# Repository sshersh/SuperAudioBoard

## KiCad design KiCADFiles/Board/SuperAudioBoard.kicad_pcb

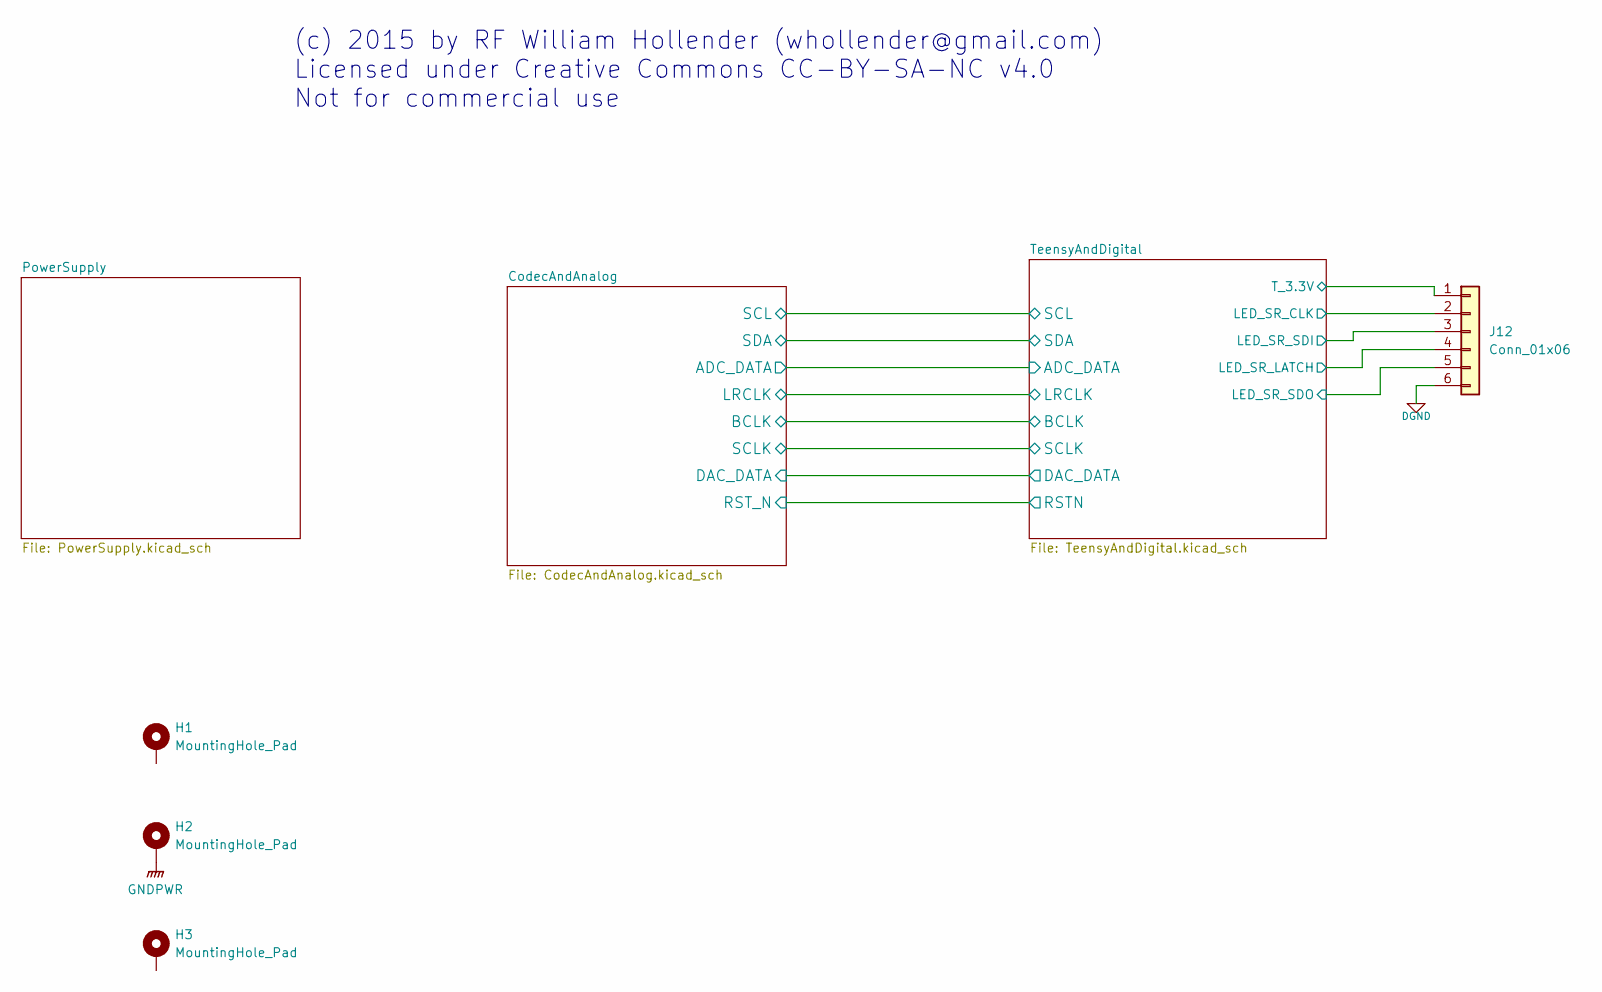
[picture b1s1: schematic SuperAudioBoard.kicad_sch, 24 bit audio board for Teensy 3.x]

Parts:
H1, H2, H3: MountingHole_Pad; MountingHole_3.2mm_M3_DIN965_Pad
J12: Conn_01x06; JST_EH_B6B-EH-A_1x06_P2.50mm_Vertical

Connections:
/TeensyAndDigital/LED_SR_CLK: J12.2; also elsewhere on the board
/TeensyAndDigital/LED_SR_LATCH: J12.4; also elsewhere on the board
/TeensyAndDigital/LED_SR_SDI: J12.3; also elsewhere on the board
/TeensyAndDigital/LED_SR_SDO: J12.5; also elsewhere on the board
/TeensyAndDigital/T_3.3V: J12.1; also elsewhere on the board
DGND: J12.6; also elsewhere on the board
GNDPWR: H2.1; also elsewhere on the board

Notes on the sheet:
(c) 2015 by RF William Hollender (whollender@gmail.com) Licensed under Creative Commons CC-BY-SA-NC v4.0 Not for commercial use

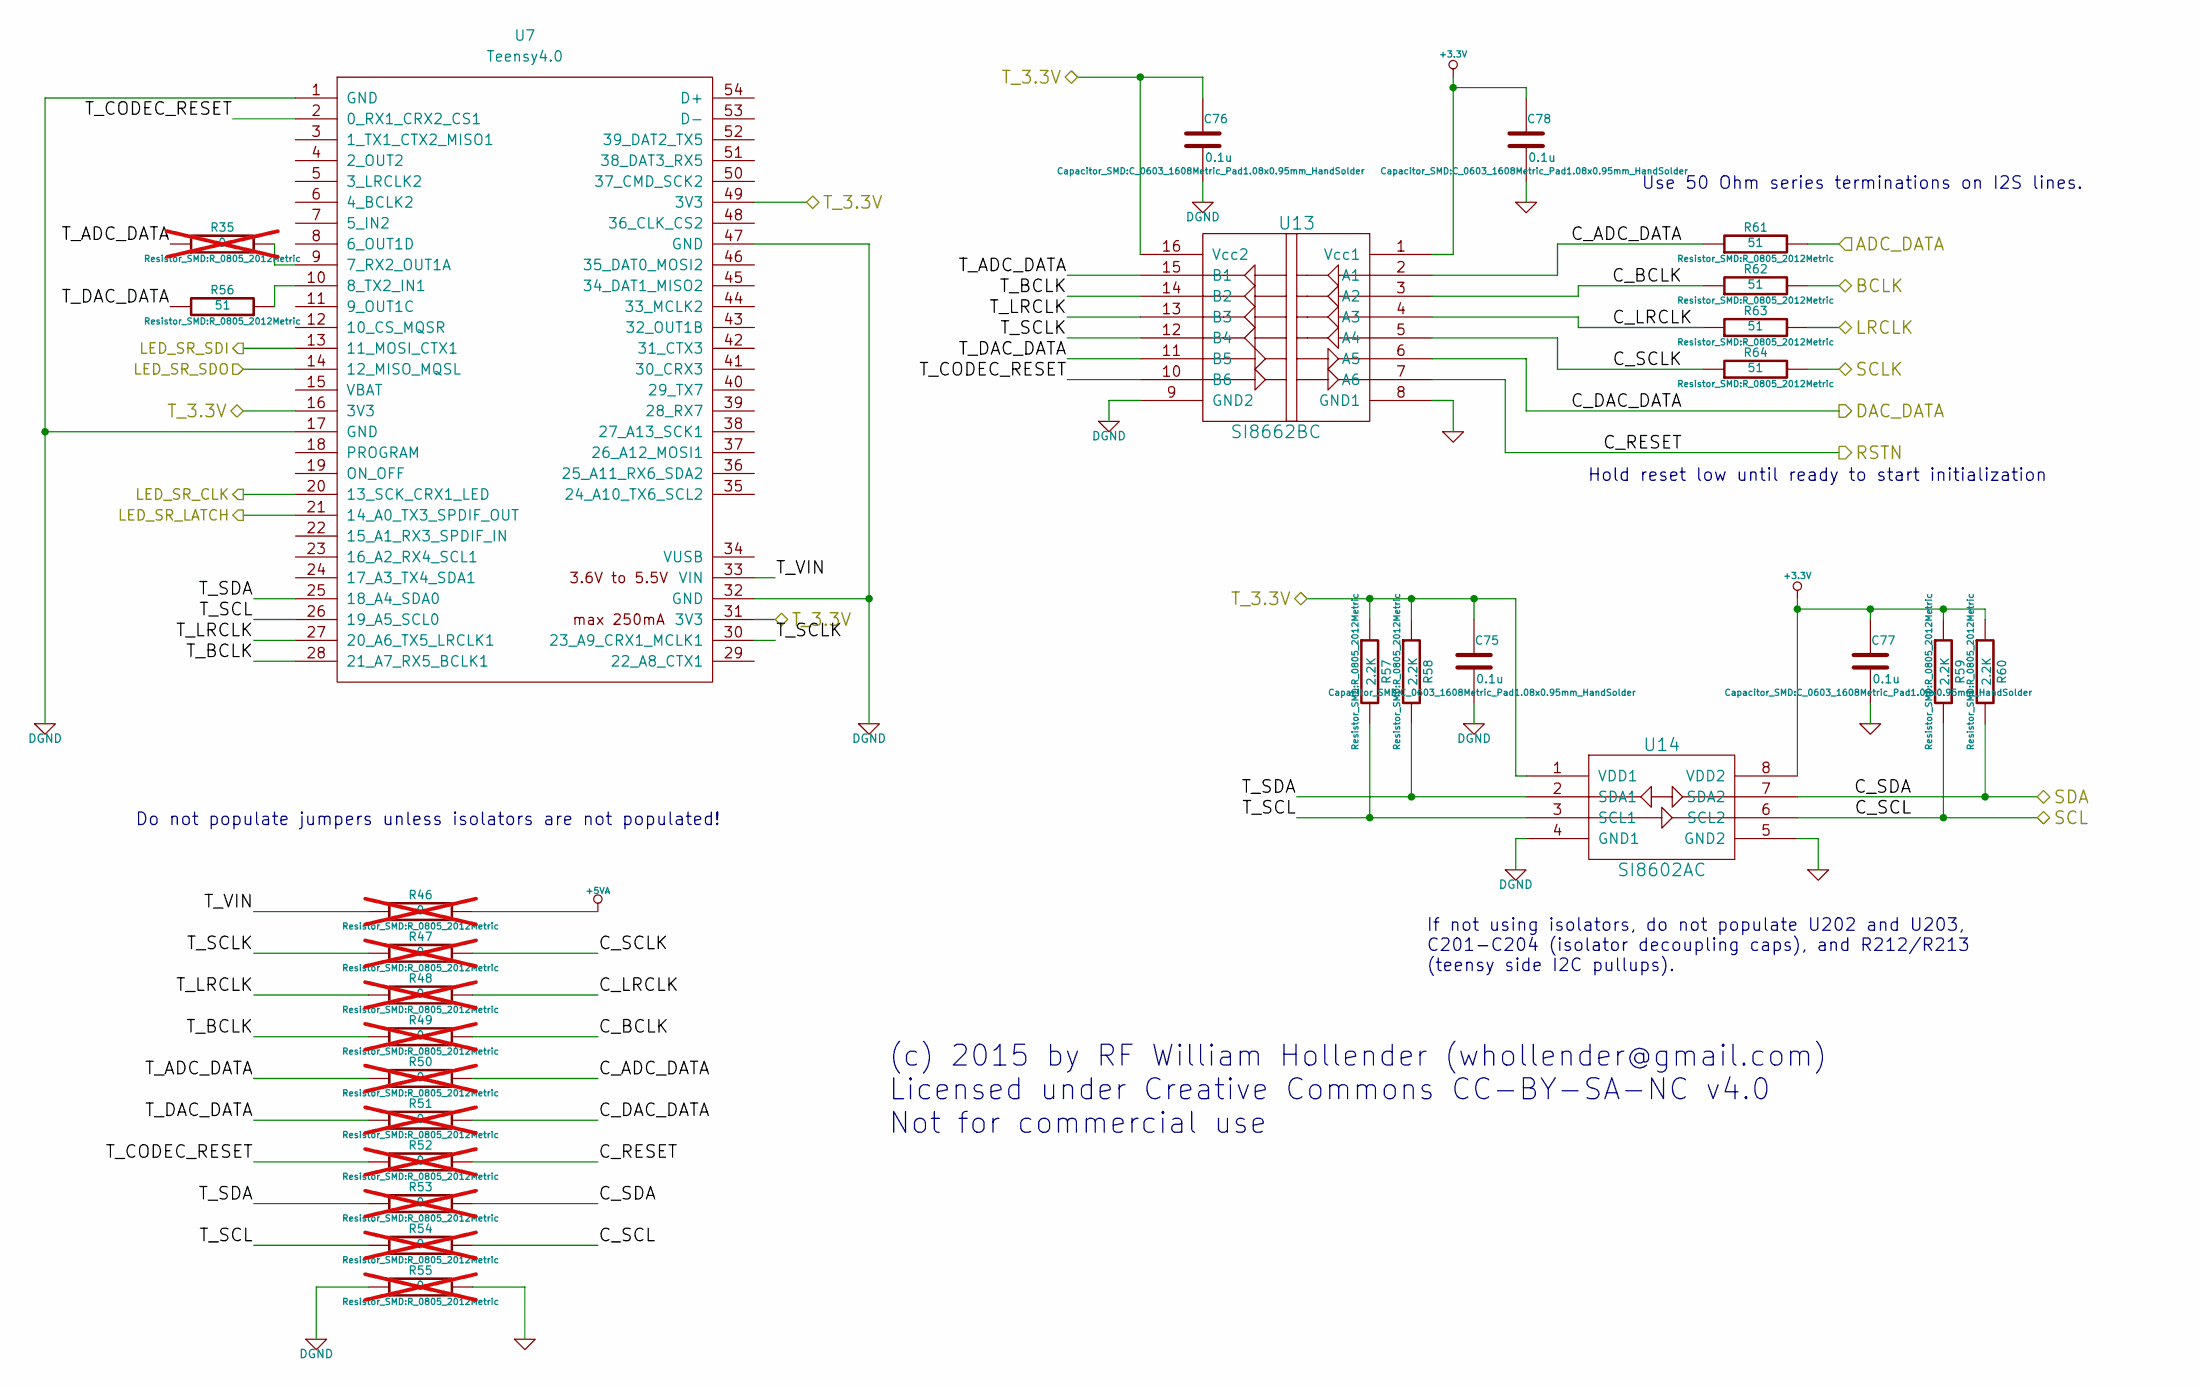
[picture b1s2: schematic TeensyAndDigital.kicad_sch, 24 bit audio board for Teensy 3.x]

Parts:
C75, C76, C77, C78: 0.1u; C_0603_1608Metric_Pad1.08x0.95mm_HandSolder; MFG1 PN GRM188R71E104KA01
R35, R46, R47, R48, R49, R50, R51, R52, R53, R54, R55: 0; R_0805_2012Metric; MFG1 PN RC0805JR-070RL; not fitted
R56, R61, R62, R63, R64: 51; R_0805_2012Metric; MFG1 PN CRCW080551R0JNEA
R57, R58, R59, R60: 2.2K; R_0805_2012Metric; MFG1 PN RC0805JR-072K2L
U7: Teensy4.0; Teensy40; MPN Teensy4.0
U13: SI8662BC; SOIC-16W_7.5x10.3mm_P1.27mm; MFG1 PN SI8662BC
U14: SI8602AC; SOIC-8_3.9x4.9mm_P1.27mm; MFG1 PN SI8602AC

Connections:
+3.3V: C77.1, C78.1, R59.1, R60.1, U13.1 (Vcc1), U14.8 (VDD2); also elsewhere on the board
+5VA: R46.2; also elsewhere on the board
/CodecAndAnalog/ADC_DATA: R61.2; also elsewhere on the board
/CodecAndAnalog/BCLK: R62.2; also elsewhere on the board
/CodecAndAnalog/LRCLK: R63.2; also elsewhere on the board
/CodecAndAnalog/SCLK: R64.2; also elsewhere on the board
/TeensyAndDigital/C_ADC_DATA: R50.2, R61.1, U13.2 (A1)
/TeensyAndDigital/C_BCLK: R49.2, R62.1, U13.3 (A2)
/TeensyAndDigital/C_DAC_DATA: R51.2, U13.6 (A5); also elsewhere on the board
/TeensyAndDigital/C_LRCLK: R48.2, R63.1, U13.4 (A3)
/TeensyAndDigital/C_RESET: R52.2, U13.7 (A6); also elsewhere on the board
/TeensyAndDigital/C_SCL: R54.2, R59.2, U14.6 (SCL2); also elsewhere on the board
/TeensyAndDigital/C_SCLK: R47.2, R64.1, U13.5 (A4)
/TeensyAndDigital/C_SDA: R53.2, R60.2, U14.7 (SDA2); also elsewhere on the board
/TeensyAndDigital/LED_SR_CLK: U7.20 (13_SCK_CRX1_LED); also elsewhere on the board
/TeensyAndDigital/LED_SR_LATCH: U7.21 (14_A0_TX3_SPDIF_OUT); also elsewhere on the board
/TeensyAndDigital/LED_SR_SDI: U7.13 (11_MOSI_CTX1); also elsewhere on the board
/TeensyAndDigital/LED_SR_SDO: U7.14 (12_MISO_MQSL); also elsewhere on the board
/TeensyAndDigital/T_3.3V: C75.1, C76.1, R57.1, R58.1, U7.16 (3V3), U7.31 (3V3), U7.49 (3V3), U13.16 (Vcc2), U14.1 (VDD1); also elsewhere on the board
/TeensyAndDigital/T_ADC_DATA: R35.1, R50.1, U13.15 (B1)
/TeensyAndDigital/T_BCLK: R49.1, U7.28 (21_A7_RX5_BCLK1), U13.14 (B2)
/TeensyAndDigital/T_CODEC_RESET: R52.1, U7.2 (0_RX1_CRX2_CS1), U13.10 (B6)
/TeensyAndDigital/T_DAC_DATA: R51.1, R56.2, U13.11 (B5)
/TeensyAndDigital/T_LRCLK: R48.1, U7.27 (20_A6_TX5_LRCLK1), U13.13 (B3)
/TeensyAndDigital/T_SCL: R54.1, R57.2, U7.26 (19_A5_SCL0), U14.3 (SCL1)
/TeensyAndDigital/T_SCLK: R47.1, U7.30 (23_A9_CRX1_MCLK1), U13.12 (B4)
/TeensyAndDigital/T_SDA: R53.1, R58.2, U7.25 (18_A4_SDA0), U14.2 (SDA1)
/TeensyAndDigital/T_VIN: R46.1, U7.33 (VIN)
DGND: C75.2, C76.2, R55.1, U7.1 (GND), U7.17 (GND), U7.32 (GND), U7.47 (GND), U13.9 (GND2), U14.4 (GND1); also elsewhere on the board
GND: C77.2, C78.2, R55.2, U13.8 (GND1), U14.5 (GND2); also elsewhere on the board
unnamed: R35.2, U7.9 (7_RX2_OUT1A)
unnamed: R56.1, U7.10 (8_TX2_IN1)

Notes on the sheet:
Do not populate jumpers unless isolators are not populated!
(c) 2015 by RF William Hollender (whollender@gmail.com) Licensed under Creative Commons CC-BY-SA-NC v4.0 Not for commercial use
If not using isolators, do not populate U202 and U203, C201-C204 (isolator decoupling caps), and R212/R213 (teensy side I2C pullups).
Use 50 Ohm series terminations on I2S lines.
Hold reset low until ready to start initialization

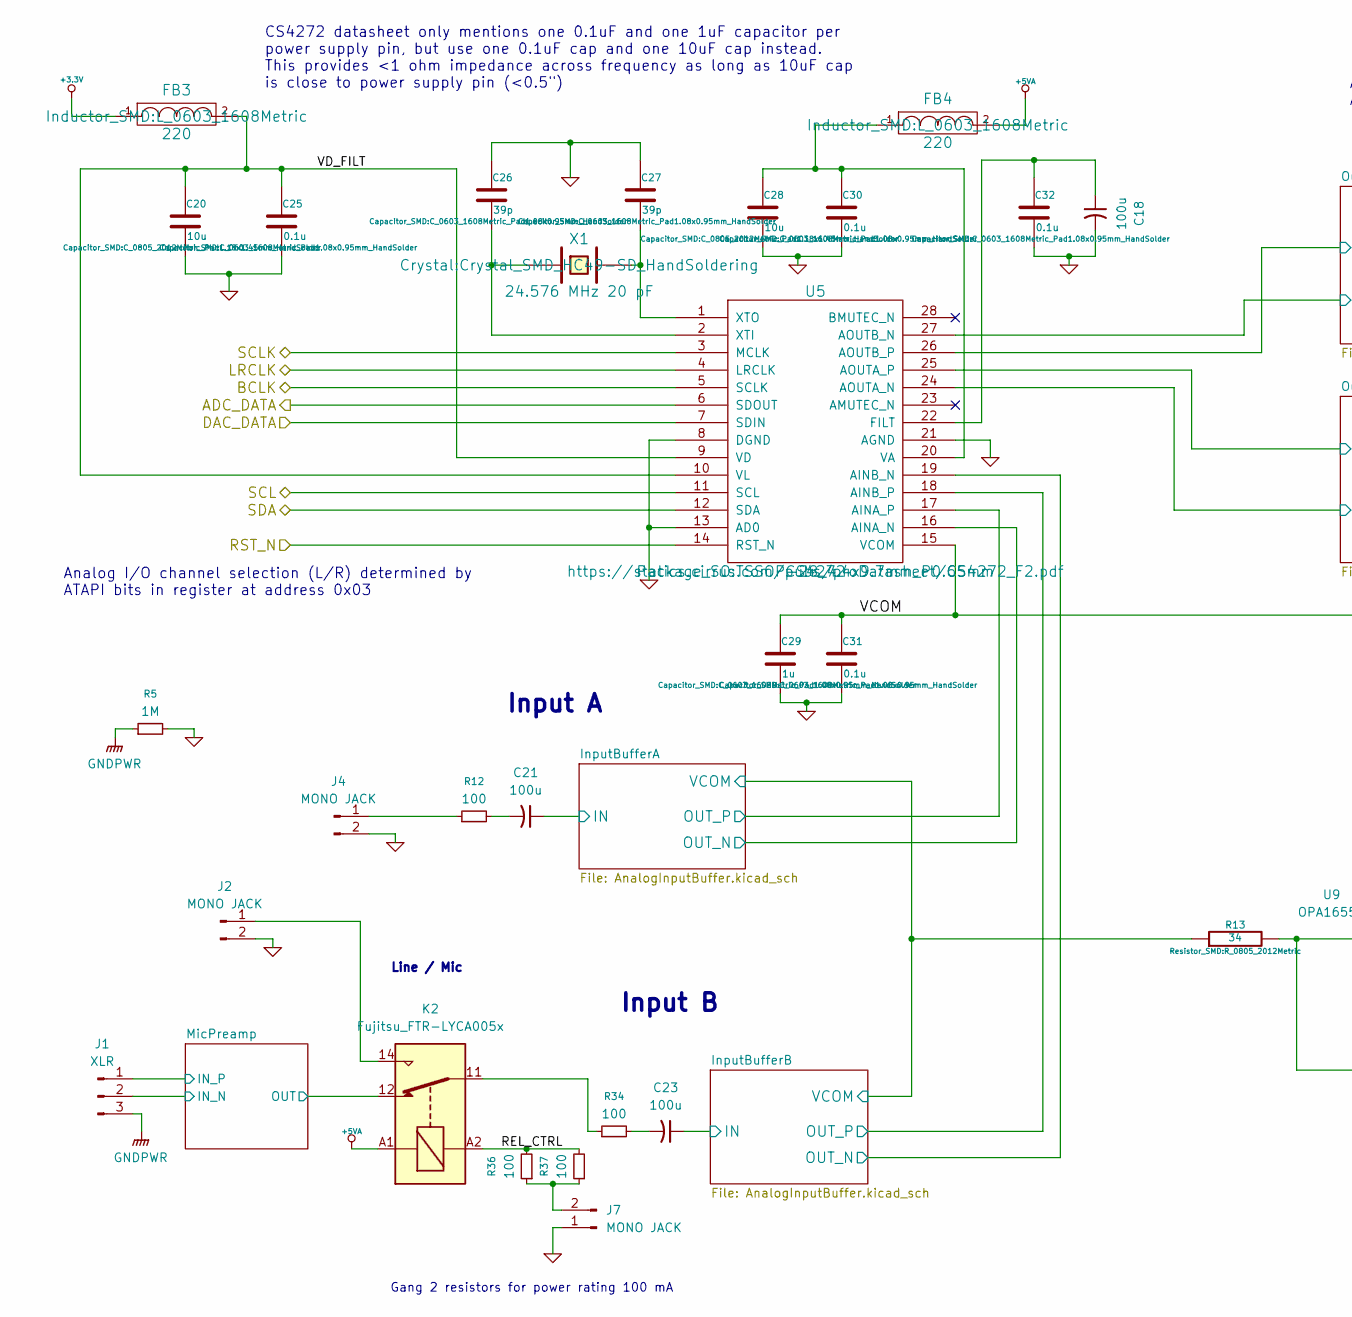
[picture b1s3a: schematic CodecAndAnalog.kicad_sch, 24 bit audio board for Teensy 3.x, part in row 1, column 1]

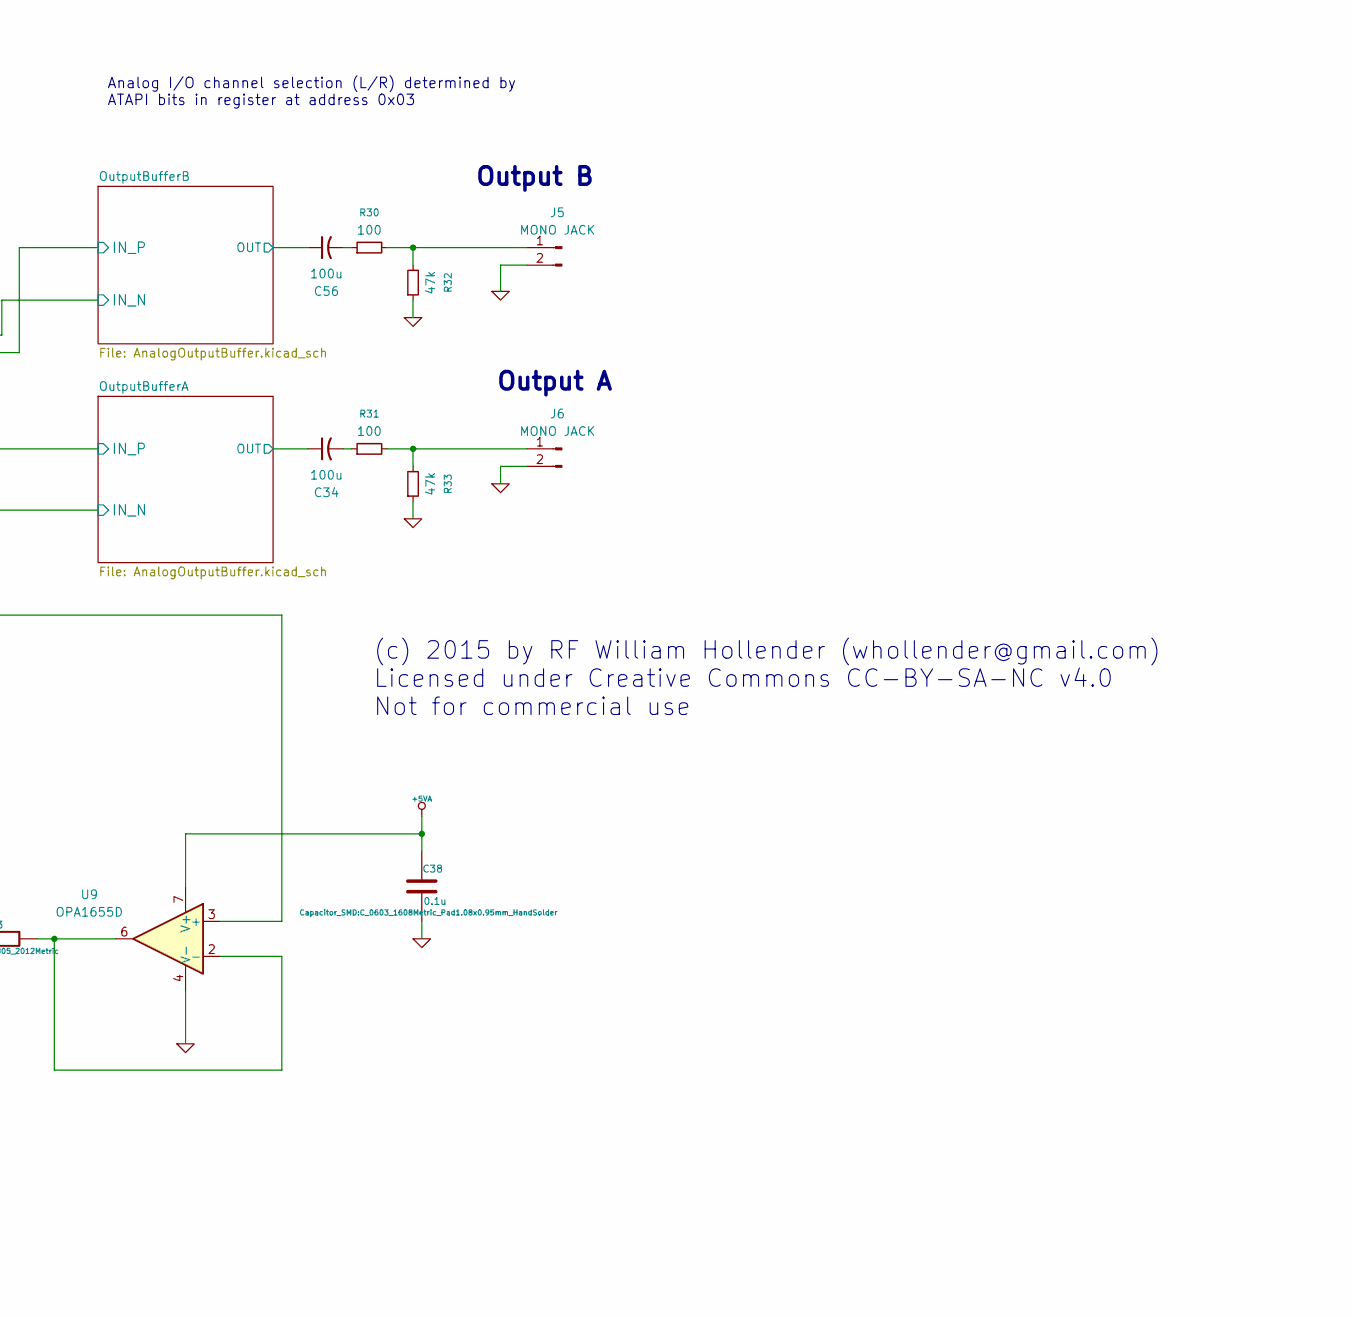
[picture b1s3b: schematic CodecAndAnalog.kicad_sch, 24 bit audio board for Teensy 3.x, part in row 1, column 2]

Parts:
C18, C21, C23, C34, C56: 100u; CP_Radial_D5.0mm_P2.00mm; MPN 25PX100MEFC5X11
C20, C28: 10u; C_0805_2012Metric_Pad1.18x1.45mm_HandSolder; Voltage 25V; MFG1 PN GRM32DR71E106KA12
C25, C30, C31, C32, C38: 0.1u; C_0603_1608Metric_Pad1.08x0.95mm_HandSolder; MFG1 PN GRM188R71E104KA01
C26, C27: 39p; C_0603_1608Metric_Pad1.08x0.95mm_HandSolder; MFG1 PN GRM1885C1H390JA01D
C29: 1u; C_0603_1608Metric_Pad1.08x0.95mm_HandSolder; MFG1 PN C2012X7R1E105K125AB
FB3, FB4: 220; L_0603_1608Metric; MFG1 PN BLM18AG221SN1
J1: XLR; PinHeader_1x03_P2.54mm_Vertical
J2, J4, J5, J6, J7: MONO JACK; PinHeader_1x02_P2.54mm_Vertical
K2: Fujitsu_FTR-LYCA005x; Relay_SPDT_Fujitsu_FTR-LYCA005x_FormC_Vertical
R5: 1M; R_0805_2012Metric
R12, R30, R31, R34, R36, R37: 100; R_0805_2012Metric; MPN CRCW0805100RFKEA
R13: 34; R_0805_2012Metric; MFG1 PN RC0805JR-0710RL
R32, R33: 47k; R_0805_2012Metric; MPN RC0805FR-0747KL
U5: CS4272; TSSOP-28_4.4x9.7mm_P0.65mm; MFG1 PN CS4272-CZZ
U9: OPA1655D; SOIC-8_3.9x4.9mm_P1.27mm; MPN OPA1655D
X1: 24.576 MHz 20 pF; Crystal_SMD_HC49-SD_HandSoldering; MFG1 PN ABM3-24.576MHZ-B2-T

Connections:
+3.3V: FB3.1; also elsewhere on the board
+5VA: C38.1, FB4.2, K2.A1, U9.7 (V+); also elsewhere on the board
/CodecAndAnalog/ADC_DATA: U5.6 (SDOUT); also elsewhere on the board
/CodecAndAnalog/BCLK: U5.5 (SCLK); also elsewhere on the board
/CodecAndAnalog/InputBufferA/OUT_N: U5.16 (AINA_N); also elsewhere on the board
/CodecAndAnalog/InputBufferA/OUT_P: U5.17 (AINA_P); also elsewhere on the board
/CodecAndAnalog/InputBufferA/VCOM: R13.1; also elsewhere on the board
/CodecAndAnalog/InputBufferA/VSIGIN: C21.1; also elsewhere on the board
/CodecAndAnalog/InputBufferB/OUT_N: U5.19 (AINB_N); also elsewhere on the board
/CodecAndAnalog/InputBufferB/OUT_P: U5.18 (AINB_P); also elsewhere on the board
/CodecAndAnalog/InputBufferB/VSIGIN: C23.1; also elsewhere on the board
/CodecAndAnalog/LRCLK: U5.4 (LRCLK); also elsewhere on the board
/CodecAndAnalog/MicPreamp/IN_N: J1.2; also elsewhere on the board
/CodecAndAnalog/MicPreamp/IN_P: J1.1; also elsewhere on the board
/CodecAndAnalog/MicPreamp/OUT: K2.12; also elsewhere on the board
/CodecAndAnalog/OutputBufferA/IN_N: U5.24 (AOUTA_N); also elsewhere on the board
/CodecAndAnalog/OutputBufferA/IN_P: U5.25 (AOUTA_P); also elsewhere on the board
/CodecAndAnalog/OutputBufferA/OUT: C34.1; also elsewhere on the board
/CodecAndAnalog/OutputBufferB/IN_N: U5.27 (AOUTB_N); also elsewhere on the board
/CodecAndAnalog/OutputBufferB/IN_P: U5.26 (AOUTB_P); also elsewhere on the board
/CodecAndAnalog/OutputBufferB/OUT: C56.1; also elsewhere on the board
/CodecAndAnalog/REL_CTRL: K2.A2, R36.2, R37.2
/CodecAndAnalog/SCLK: U5.3 (MCLK); also elsewhere on the board
/CodecAndAnalog/VCOM: C29.1, C31.1, U5.15 (VCOM), U9.3 (+)
/CodecAndAnalog/VD_FILT: C20.1, C25.1, FB3.2, U5.9 (VD), U5.10 (VL)
/TeensyAndDigital/C_DAC_DATA: U5.7 (SDIN); also elsewhere on the board
/TeensyAndDigital/C_RESET: U5.14 (RST_N); also elsewhere on the board
/TeensyAndDigital/C_SCL: U5.11 (SCL); also elsewhere on the board
/TeensyAndDigital/C_SDA: U5.12 (SDA); also elsewhere on the board
GND: C18.2, C20.2, C25.2, C26.1, C27.1, C28.2, C29.2, C30.2, C31.2, C32.2, C38.2, J2.2, J4.2, J5.2, J6.2, J7.1, R5.2, R32.1, R33.1, U5.8 (DGND), U5.13 (AD0), U5.21 (AGND), U9.4 (V-); also elsewhere on the board
GNDPWR: J1.3, R5.1; also elsewhere on the board
unnamed: C21.2, R12.2
unnamed: C23.2, R34.2
unnamed: C34.2, R31.1
unnamed: C56.2, R30.1
unnamed: J2.1, K2.14
unnamed: J4.1, R12.1
unnamed: J5.1, R30.2, R32.2
unnamed: J6.1, R31.2, R33.2
unnamed: J7.2, R36.1, R37.1
unnamed: K2.11, R34.1
unnamed: C18.1, C32.1, U5.22 (FILT)
unnamed: C28.1, C30.1, FB4.1, U5.20 (VA)
unnamed: C26.2, U5.2 (XTI), X1.1
unnamed: C27.2, U5.1 (XTO), X1.2
unnamed: R13.2, U9.2 (-), U9.6

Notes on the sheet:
Gang 2 resistors for power rating 100 mA
Output B
CS4272 datasheet only mentions one 0.1uF and one 1uF capacitor per power supply pin, but use one 0.1uF cap and one 10uF cap instead. This provides <1 ohm impedance across frequency as long as 10uF cap is close to power supply pin (<0.5")
Input B
(c) 2015 by RF William Hollender (whollender@gmail.com) Licensed under Creative Commons CC-BY-SA-NC v4.0 Not for commercial use
Analog I/O channel selection (L/R) determined by ATAPI bits in register at address 0x03
Line / Mic
Output A
Input A

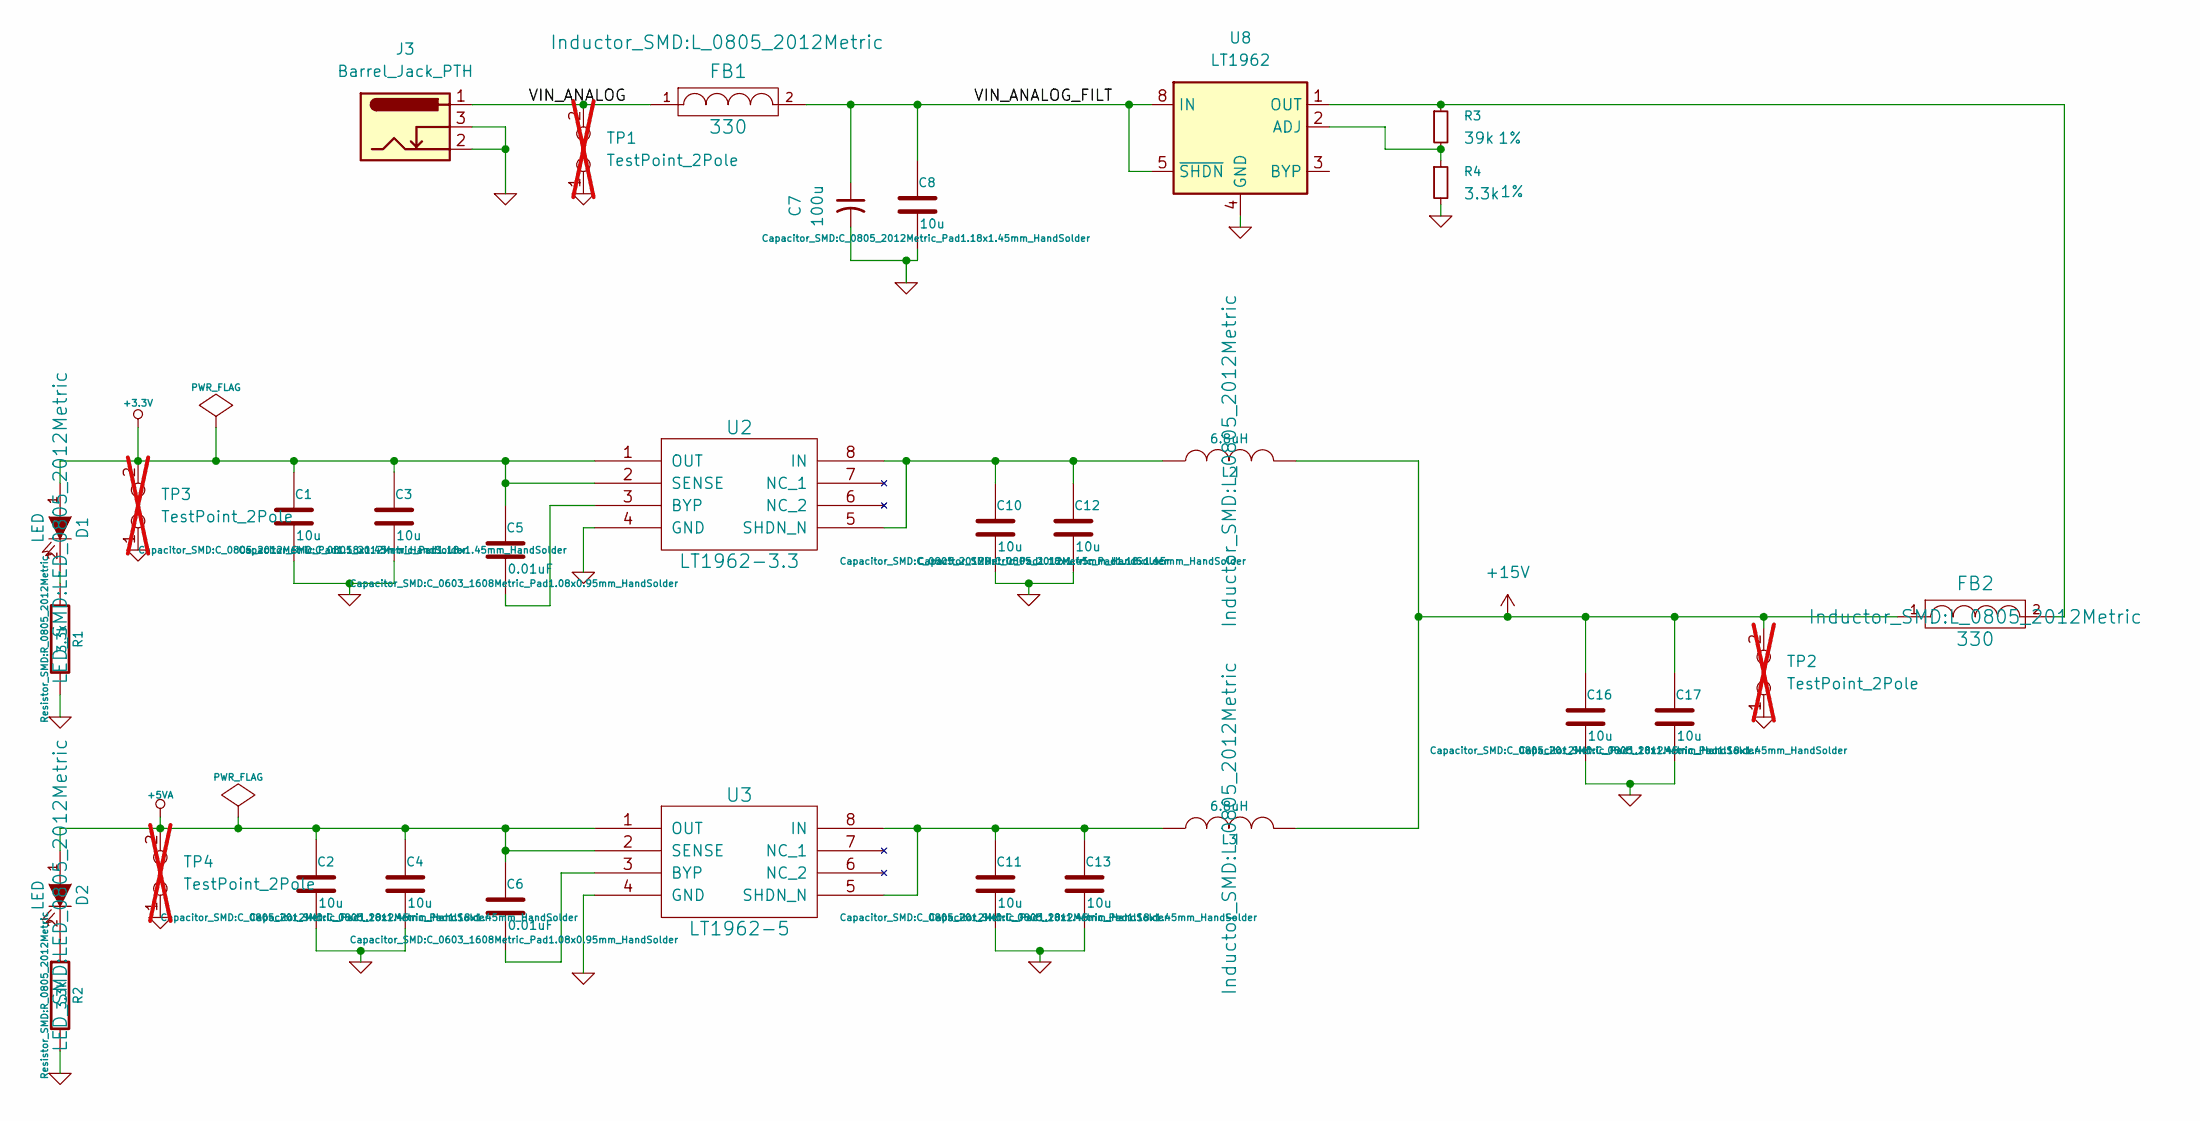
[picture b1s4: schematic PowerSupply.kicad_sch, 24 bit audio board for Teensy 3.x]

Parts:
C1, C2, C3, C4, C8, C10, C11, C12, C13, C16, C17: 10u; C_0805_2012Metric_Pad1.18x1.45mm_HandSolder; Voltage 25V; MFG1 PN GRM32DR71E106KA12
C5, C6: 0.01uF; C_0603_1608Metric_Pad1.08x0.95mm_HandSolder; MFG1 PN GRM2195C1H103JA01D
C7: 100u; CP_Radial_D5.0mm_P2.00mm; MPN 25PX100MEFC5X11
D1, D2: LED; LED_0805_2012Metric; MFG1 PN APT2012CGCK
FB1, FB2: 330; L_0805_2012Metric; MFG1 PN BLM21PG331SN1D
J3: Barrel_Jack_PTH
L2, L3: 6.8uH; L_0805_2012Metric; MFG1 PN MSS1038-522NLB
R1: 3.3k; R_0805_2012Metric; MFG1 PN ERJ-6GEYJ271V
R2: 3.3k; R_0805_2012Metric; MFG1 PN ERJ-6GEYJ621V
R3: 39k; R_0805_2012Metric; MPN ERA-6AEB3922V
R4: 3.3k; R_0805_2012Metric; MPN ERA-6AEB332V
TP1, TP2, TP3, TP4: TestPoint_2Pole; TestPoint_2Pads_Pitch2.54mm_Drill0.8mm; not fitted
U2: LT1962-3.3; MSOP-8_3x3mm_P0.65mm; MFG1 PN LT1962EMS8-3.3#PBF
U3: LT1962-5; MSOP-8_3x3mm_P0.65mm; MFG1 PN LT1962EMS8-5#PBF-ND
U8: LT1962; MSOP-8_3x3mm_P0.65mm; MPN LT1962EMS8

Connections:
+3.3V: C1.1, C3.1, C5.1, D1.1 (A), TP3.2, U2.1 (OUT), U2.2 (SENSE); also elsewhere on the board
+5VA: C2.1, C4.1, C6.1, D2.1 (A), TP4.2, U3.1 (OUT), U3.2 (SENSE); also elsewhere on the board
+15V: C16.1, C17.1, FB2.1, L2.2, L3.2, TP2.2; also elsewhere on the board
/PowerSupply/VIN_ANALOG: FB1.1, J3.1 (PWR), TP1.2
/PowerSupply/VIN_ANALOG_FILT: C7.1, C8.1, FB1.2, U8.5 (~SHDN), U8.8 (IN)
GND: C1.2, C2.2, C3.2, C4.2, C7.2, C8.2, C10.2, C11.2, C12.2, C13.2, C16.2, C17.2, J3.2 (GND), J3.3 (GNDBREAK), R1.2, R2.2, R4.2, TP1.1, TP2.1, TP3.1, TP4.1, U2.4 (GND), U3.4 (GND), U8.4 (GND); also elsewhere on the board
unnamed: D1.2 (K), R1.1
unnamed: D2.2 (K), R2.1
unnamed: C5.2, U2.3 (BYP)
unnamed: C10.1, C12.1, L2.1, U2.5 (SHDN_N), U2.8 (IN)
unnamed: C6.2, U3.3 (BYP)
unnamed: C11.1, C13.1, L3.1, U3.5 (SHDN_N), U3.8 (IN)
unnamed: R3.2, R4.1, U8.2 (ADJ)
unnamed: FB2.2, R3.1, U8.1 (OUT)

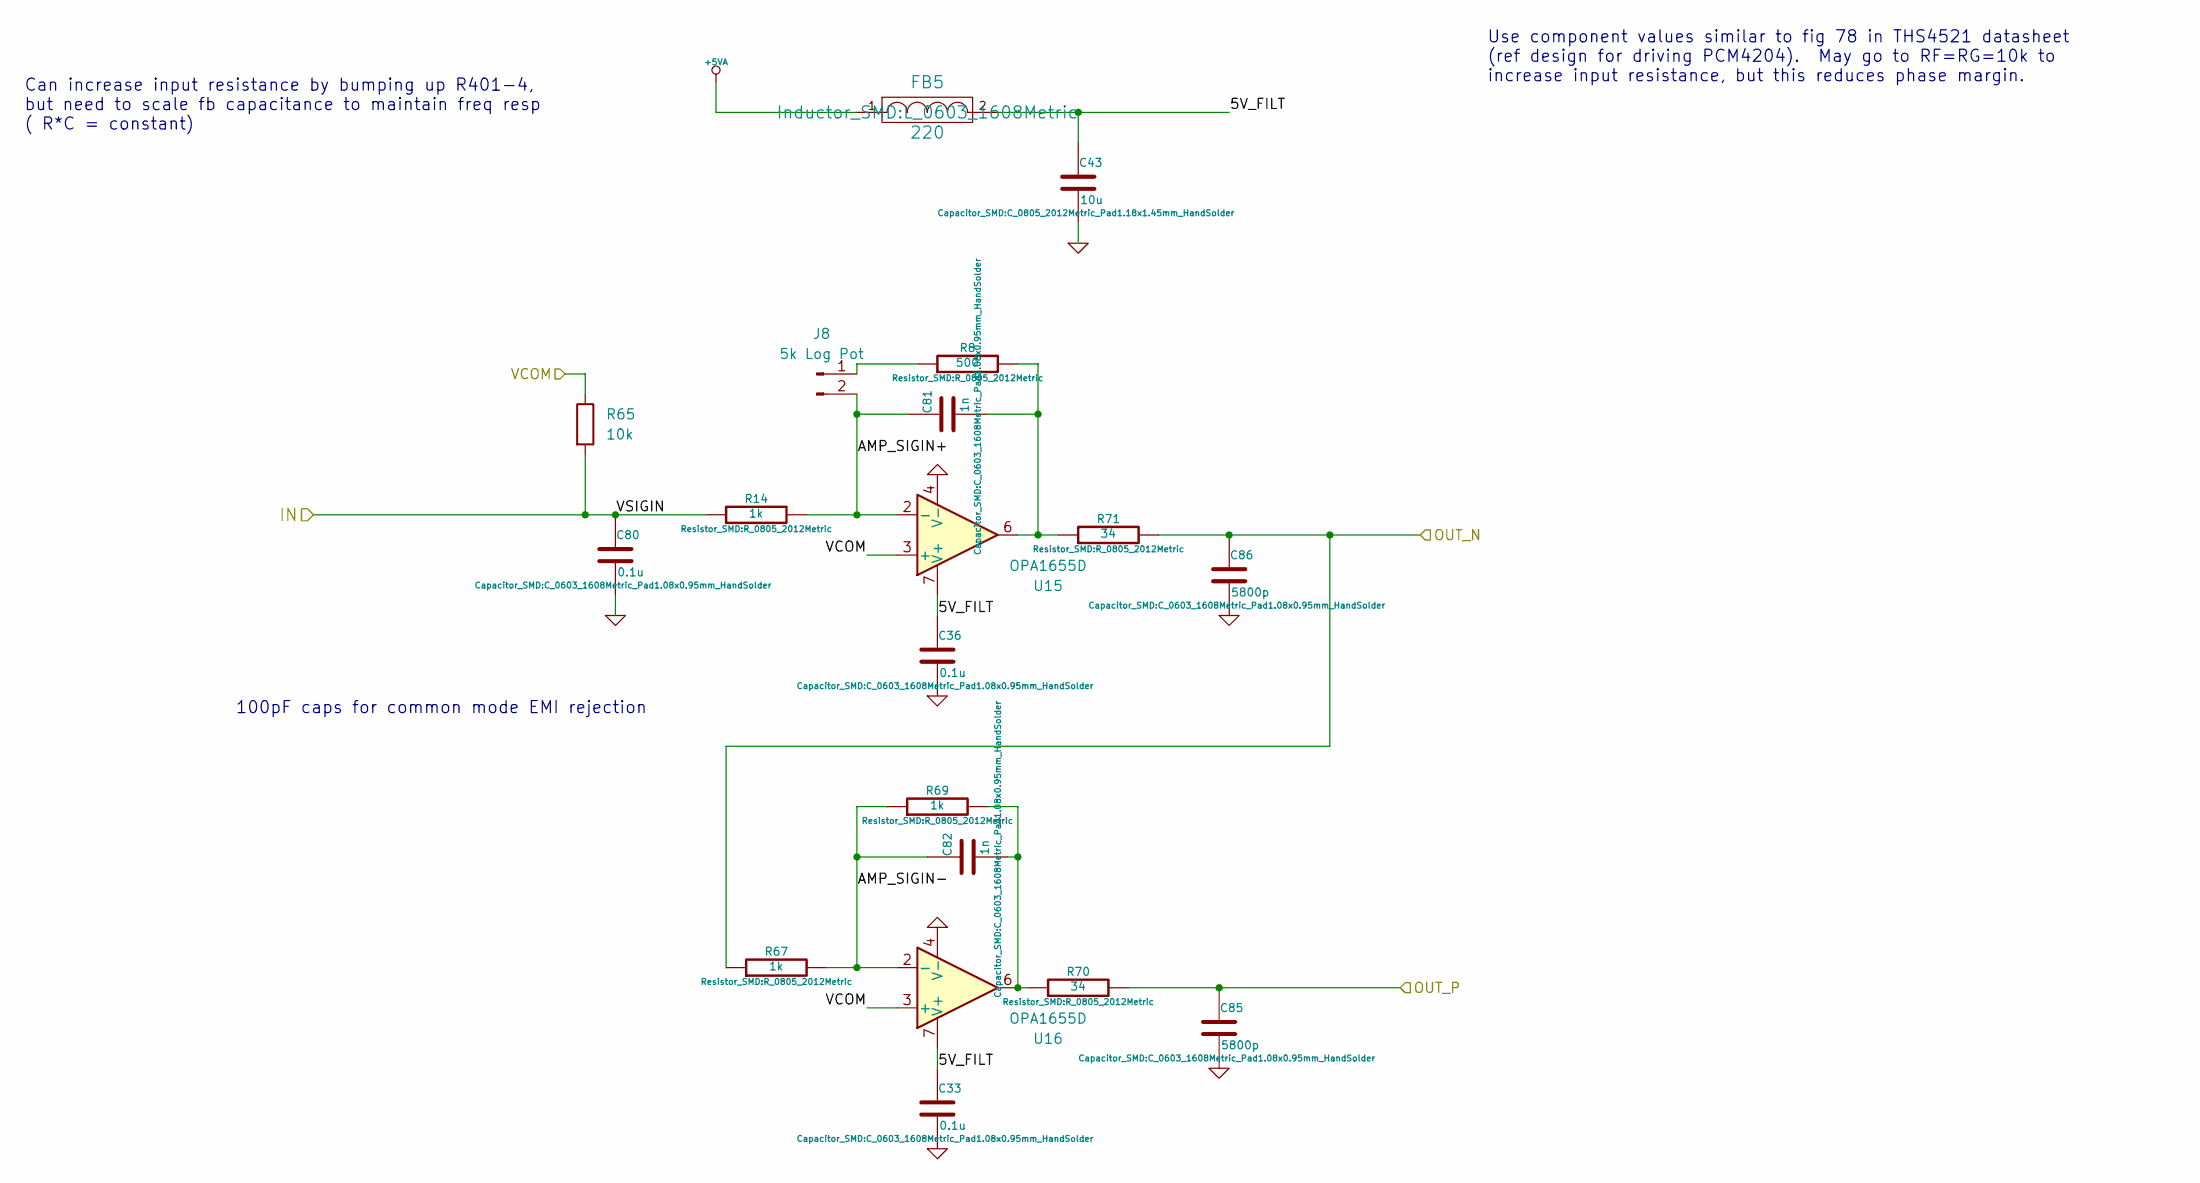
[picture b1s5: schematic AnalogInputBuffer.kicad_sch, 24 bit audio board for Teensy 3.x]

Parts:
C33, C36: 0.1u; C_0603_1608Metric_Pad1.08x0.95mm_HandSolder; MFG1 PN GRM188R71E104KA01
C43: 10u; C_0805_2012Metric_Pad1.18x1.45mm_HandSolder; Voltage 25V; MFG1 PN GRM32DR71E106KA12
C80: 0.1u; C_0603_1608Metric_Pad1.08x0.95mm_HandSolder; MFG1 PN GRM1885C1H101JA01D
C81, C82: 1n; C_0603_1608Metric_Pad1.08x0.95mm_HandSolder; MFG1 PN GRM2165C1H102FA01D
C85, C86: 5800p; C_0603_1608Metric_Pad1.08x0.95mm_HandSolder; MFG1 PN GRM2165C1H272JA01D
FB5: 220; L_0603_1608Metric; MFG1 PN BLM18AG221SN1
J8: 5k Log Pot; PinHeader_1x02_P2.54mm_Vertical; MPN RV16AF-10-15K-C5K-3LA
R8: 500; R_0805_2012Metric; MFG1 PN RG2012P-102-B-T5
R14, R67, R69: 1k; R_0805_2012Metric; MFG1 PN RG2012P-102-B-T5
R65: 10k; R_0805_2012Metric; MPN CRCW080510K0FKEA
R70, R71: 34; R_0805_2012Metric; MFG1 PN RR1220Q-40R2-D-M
U15, U16: OPA1655D; SOIC-8_3.9x4.9mm_P1.27mm; MPN OPA1655D

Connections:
+5VA: FB5.1; also elsewhere on the board
/CodecAndAnalog/InputBufferA/5V_FILT: C33.1, C36.1, C43.1, FB5.2, U15.7 (V+), U16.7 (V+)
/CodecAndAnalog/InputBufferA/AMP_SIGIN+: C81.1, J8.2, R14.2, U15.2 (-)
/CodecAndAnalog/InputBufferA/AMP_SIGIN-: C82.1, R67.2, R69.1, U16.2 (-)
/CodecAndAnalog/InputBufferA/OUT_N: C86.1, R67.1, R71.2; also elsewhere on the board
/CodecAndAnalog/InputBufferA/OUT_P: C85.1, R70.2; also elsewhere on the board
/CodecAndAnalog/InputBufferA/VCOM: R65.1, U15.3 (+), U16.3 (+); also elsewhere on the board
/CodecAndAnalog/InputBufferA/VSIGIN: C80.1, R14.1, R65.2; also elsewhere on the board
GND: C33.2, C36.2, C43.2, C80.2, C85.2, C86.2, U15.4 (V-), U16.4 (V-); also elsewhere on the board
unnamed: C81.2, R8.2, R71.1, U15.6
unnamed: C82.2, R69.2, R70.1, U16.6
unnamed: J8.1, R8.1

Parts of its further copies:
C35, C37: 0.1u; C_0603_1608Metric_Pad1.08x0.95mm_HandSolder; MFG1 PN GRM188R71E104KA01
C52: 10u; C_0805_2012Metric_Pad1.18x1.45mm_HandSolder; Voltage 25V; MFG1 PN GRM32DR71E106KA12
C90: 0.1u; C_0603_1608Metric_Pad1.08x0.95mm_HandSolder; MFG1 PN GRM1885C1H101JA01D
C91, C92: 1n; C_0603_1608Metric_Pad1.08x0.95mm_HandSolder; MFG1 PN GRM2165C1H102FA01D
C95, C96: 5800p; C_0603_1608Metric_Pad1.08x0.95mm_HandSolder; MFG1 PN GRM2165C1H272JA01D
FB6: 220; L_0603_1608Metric; MFG1 PN BLM18AG221SN1
J9: 5k Log Pot; PinHeader_1x02_P2.54mm_Vertical; MPN RV16AF-10-15K-C5K-3LA
R9: 500; R_0805_2012Metric; MFG1 PN RG2012P-102-B-T5
R15, R76, R78: 1k; R_0805_2012Metric; MFG1 PN RG2012P-102-B-T5
R74: 10k; R_0805_2012Metric; MPN CRCW080510K0FKEA
R79, R80: 34; R_0805_2012Metric; MFG1 PN RR1220Q-40R2-D-M
U17, U18: OPA1655D; SOIC-8_3.9x4.9mm_P1.27mm; MPN OPA1655D

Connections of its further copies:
+5VA: FB6.1; also elsewhere on the board
/CodecAndAnalog/InputBufferA/VCOM: R74.1, U17.3 (+), U18.3 (+); also elsewhere on the board
/CodecAndAnalog/InputBufferB/5V_FILT: C35.1, C37.1, C52.1, FB6.2, U17.7 (V+), U18.7 (V+)
/CodecAndAnalog/InputBufferB/AMP_SIGIN+: C91.1, J9.2, R15.2, U17.2 (-)
/CodecAndAnalog/InputBufferB/AMP_SIGIN-: C92.1, R76.2, R78.1, U18.2 (-)
/CodecAndAnalog/InputBufferB/OUT_N: C96.1, R76.1, R80.2; also elsewhere on the board
/CodecAndAnalog/InputBufferB/OUT_P: C95.1, R79.2; also elsewhere on the board
/CodecAndAnalog/InputBufferB/VSIGIN: C90.1, R15.1, R74.2; also elsewhere on the board
GND: C35.2, C37.2, C52.2, C90.2, C95.2, C96.2, U17.4 (V-), U18.4 (V-); also elsewhere on the board
unnamed: C91.2, R9.2, R80.1, U17.6
unnamed: C92.2, R78.2, R79.1, U18.6
unnamed: J9.1, R9.1

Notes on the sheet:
Use component values similar to fig 78 in THS4521 datasheet (ref design for driving PCM4204). May go to RF=RG=10k to increase input resistance, but this reduces phase margin.
100pF caps for common mode EMI rejection
Can increase input resistance by bumping up R401-4, but need to scale fb capacitance to maintain freq resp ( R*C = constant)
